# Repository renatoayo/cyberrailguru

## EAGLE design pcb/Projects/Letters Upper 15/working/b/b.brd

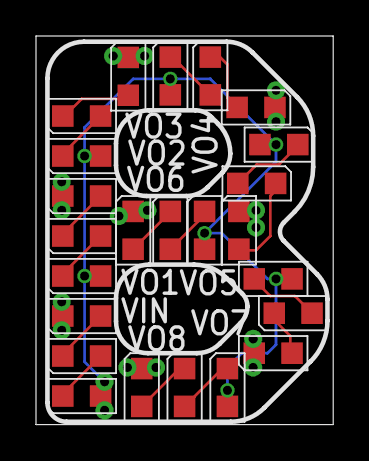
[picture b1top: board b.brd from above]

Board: 2 copper layers, 16.5 x 21.6 mm, 42 parts (0 on the bottom side), 25 nets.

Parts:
LED1, LED2, LED3, LED4, LED5, LED6, LED7, LED8, LED9, LED10, LED11, LED12, LED13, LED14, LED15, LED16, LED17, LED18, LED19, LED20, LED21, LED22, LED23, LED24: LED_0805
VIN, VIN1: P1-20
VO1, VO2, VO3, VO4, VO5, VO6, VO7, VO8, VO9, VO10, VO11, VO12, VO13, VO14, VO15, VO16: P1-20

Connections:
unnamed: LED22.C, LED23.A
unnamed: LED23.C, LED24.A
unnamed: LED2.C, LED3.A
unnamed: LED1.C, LED2.A
unnamed: LED24.C, VO8.TP, VO16.TP
unnamed: LED5.C, LED6.A
unnamed: LED4.C, LED5.A
unnamed: LED8.C, LED9.A
unnamed: LED7.C, LED8.A
unnamed: LED11.C, LED12.A
unnamed: LED10.C, LED11.A
unnamed: LED14.C, LED15.A
unnamed: LED13.C, LED14.A
unnamed: LED17.C, LED18.A
unnamed: LED16.C, LED17.A
unnamed: LED20.C, LED21.A
unnamed: LED19.C, LED20.A
VIN: LED1.A, LED4.A, LED7.A, LED10.A, LED13.A, LED16.A, LED19.A, LED22.A, VIN.TP, VIN1.TP
VOUT1: LED3.C, VO1.TP, VO9.TP
VOUT2: LED6.C, VO2.TP, VO10.TP
VOUT3: LED9.C, VO3.TP, VO11.TP
VOUT4: LED12.C, VO4.TP, VO12.TP
VOUT5: LED15.C, VO5.TP, VO13.TP
VOUT6: LED18.C, VO6.TP, VO14.TP
VOUT7: LED21.C, VO7.TP, VO15.TP

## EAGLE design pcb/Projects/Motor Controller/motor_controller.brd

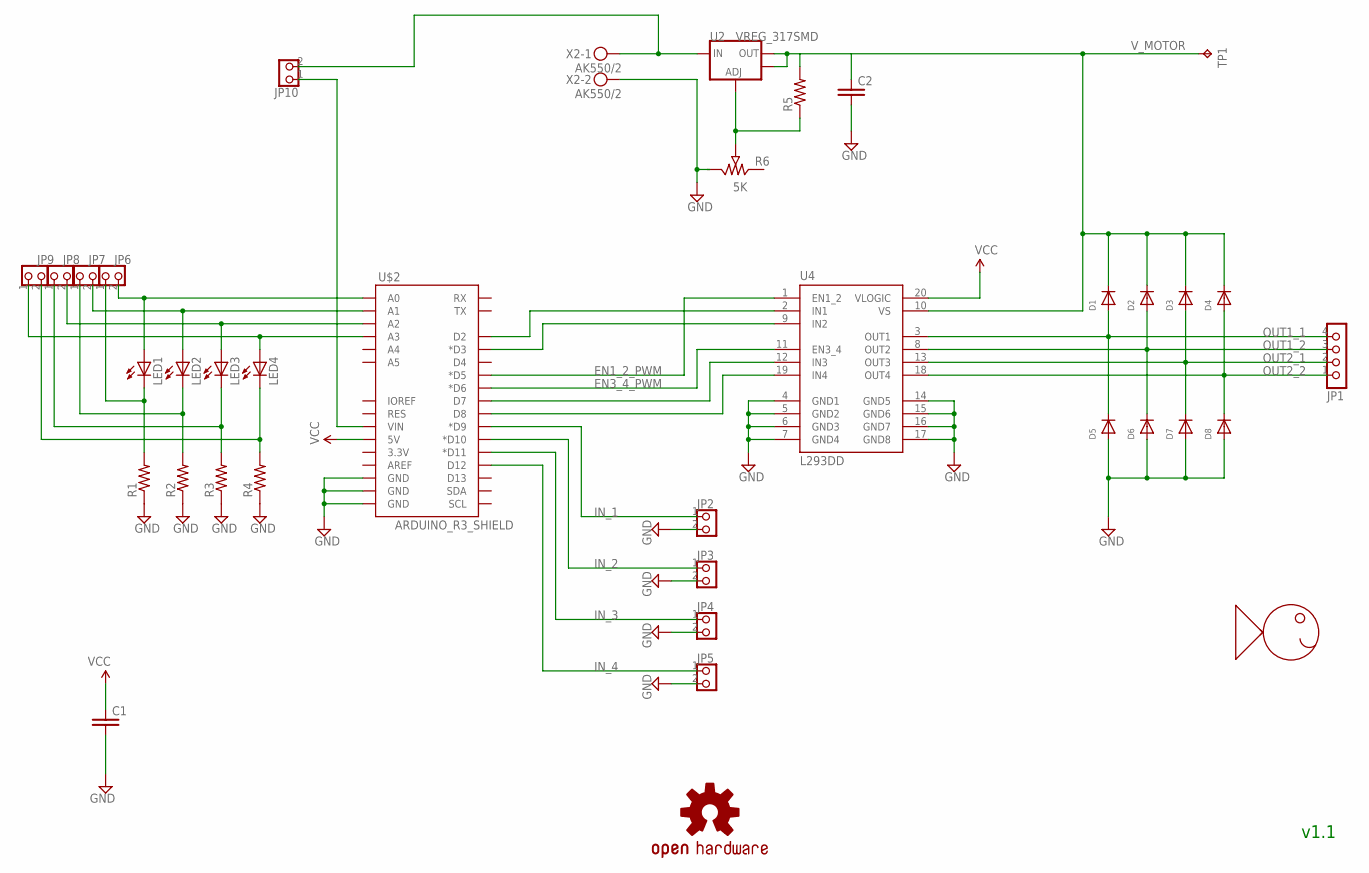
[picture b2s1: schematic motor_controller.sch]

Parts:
C1, C2: CAPACITORC0603; C0603
D1, D2, D3, D4, D5, D6, D7, D8: DIODESOD-123; SOD-123
JP1: PINHD-1X4/90; 1X04/90
JP2, JP3, JP4, JP5, JP6, JP7, JP8, JP9, JP10: PINHD-1X2; 1X02
LED1, LED2, LED3, LED4: LED0805; LED_0805
LOGO1: OSHW-LOGOM; OSHW-LOGO-M
R1, R2, R3, R4, R5: RESISTOR_SMD0603-RES; 0603-RES
R6: 5K; BOURNS_3362H
TP1: TEST_POINTPAD1-20; P1-20
U2: VREG_317SMD; SOT223
U4: L293DD; SO20
U$1: FHI_LOGO
U$2: ARDUINO_R3_SHIELD; UNO_R3_SHIELD
X2: AK550/2

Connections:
EN1_2_PWM: U4.1 (EN1_2), U$2.D5 (*D5)
EN3_4_PWM: U4.11 (EN3_4), U$2.D6 (*D6)
GND: C1.2, C2.2, D5.A, D6.A, D7.A, D8.A, JP2.2, JP3.2, JP4.2, JP5.2, R1.1, R2.1, R3.1, R4.1, R6.3, U4.4 (GND1), U4.5 (GND2), U4.6 (GND3), U4.7 (GND4), U4.14 (GND5), U4.15 (GND6), U4.16 (GND7), U4.17 (GND8), U$2.GND@0 (GND), U$2.GND@1 (GND), U$2.GND@2 (GND), X2.2
IN1: U4.2 (IN1), U$2.D2
IN2: U4.9 (IN2), U$2.D3 (*D3)
IN3: U4.12 (IN3), U$2.D7
IN4: U4.19 (IN4), U$2.D8
IN_1: JP2.1, U$2.D9 (*D9)
IN_2: JP3.1, U$2.D10 (*D10)
IN_3: JP4.1, U$2.D11 (*D11)
IN_4: JP5.1, U$2.D12
unnamed: JP10.1, U$2.VIN
unnamed: JP6.2, LED1.A, U$2.A0
unnamed: JP7.2, LED2.A, U$2.A1
unnamed: JP8.2, LED3.A, U$2.A2
unnamed: JP9.1, LED4.A, U$2.A3
unnamed: JP10.2, U2.3 (IN), X2.1
unnamed: JP9.2, LED4.C, R4.2
unnamed: R5.1, R6.2, U2.1 (ADJ)
unnamed: JP8.1, LED3.C, R3.2
unnamed: JP7.1, LED2.C, R2.2
unnamed: JP6.1, LED1.C, R1.2
OUT1_1: D1.A, D5.C, JP1.4, U4.3 (OUT1)
OUT1_2: D2.A, D6.C, JP1.3, U4.8 (OUT2)
OUT2_1: D3.A, D7.C, JP1.2, U4.13 (OUT3)
OUT2_2: D4.A, D8.C, JP1.1, U4.18 (OUT4)
VCC: C1.1, U4.20 (VLOGIC), U$2.5V
V_MOTOR: C2.1, D1.C, D2.C, D3.C, D4.C, R5.2, TP1.TP, U2.2 (OUT1), U2.4 (OUT2), U4.10 (VS)

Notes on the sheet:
v1.1

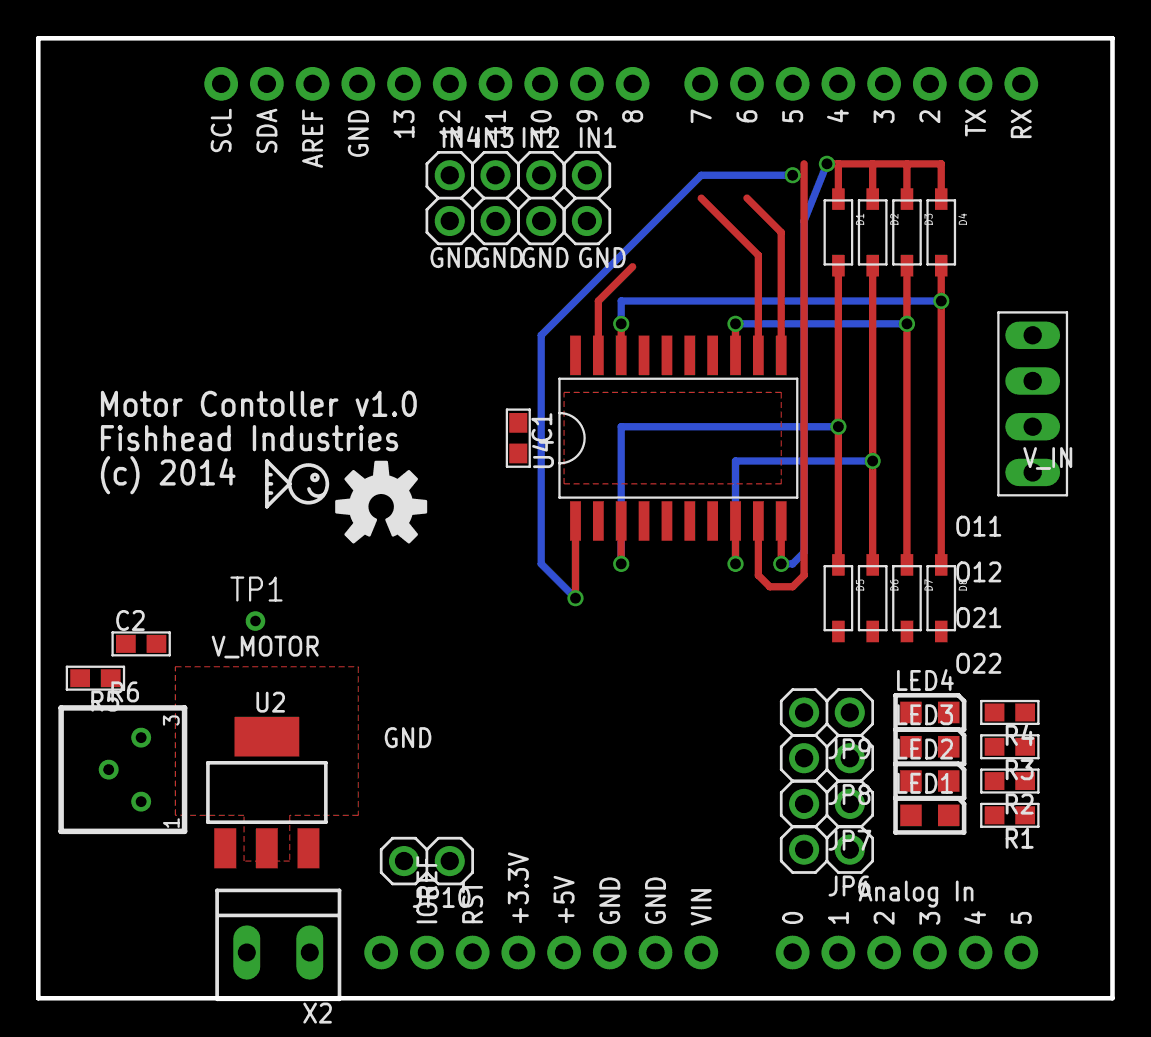
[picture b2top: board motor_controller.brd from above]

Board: 2 copper layers, 59.7 x 53.3 mm, 37 parts (0 on the bottom side), 28 nets.

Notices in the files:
pcb/Projects/Motor Controller/motor_controller.brd:
(c) 2014
parts and their libraries:
SparkFun-Aesthetics: Licensing: CC v3.0 Share-Alike You are welcome to use this library for commercial purposes.
